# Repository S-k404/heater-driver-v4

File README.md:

<!-- datasheet:banner -->
<p align="center">
  <picture>
    <source media="(prefers-color-scheme: dark)" srcset=".github/assets/banner-dark.svg">
    
  </picture>
</p>
<!-- /datasheet:banner -->

# Heater Driver 12 V / 100 W — v4 (All Through-Hole, Runs Cool, OCP + OTP)

Rev 4.0 · 2026-10-17 · KiCad 9.0 project · 2-layer, **54 × 42 mm** · **100 % through-hole parts**

v4 builds on v3 with three goals:
1. **It can't cook itself.** It uses a 1.3 mΩ MOSFET and adds over-temperature shutdown on top of overcurrent shutdown.
2. **Every part is through-hole.**
3. **A step-by-step placement guide** shows where every part goes.

Start with **`docs/heater_driver_v4_placement_guide.pdf`**.

---

<!-- datasheet:figure -->
## At a glance

<p align="center">
  <picture>
    <source media="(prefers-color-scheme: dark)" srcset=".github/assets/diagram-dark.svg">
    
  </picture>
</p>

| Characteristic | Detail |
| --- | --- |
| **Rating** | 12 V, 100 W (8.33 A) into a heater load; 2-layer board, 54 × 42 mm, 100 % through-hole |
| **Switch** | 1.3 mΩ MOSFET Q1 dissipating about 0.09 W at full load |
| **Protection** | Latching overcurrent (gate off about 7 µs after a short), latching over-temperature at about 84 °C, 15 A fuse, TVS clamp |
| **Verification** | Copper current check to IPC-2221, simulation reports and a step-by-step placement guide in `docs/` |
<!-- /datasheet:figure -->

## 1. Folder contents

| Path | What it is |
|---|---|
| `docs/heater_driver_v4_placement_guide.pdf` | **Assembly guide.** Board map, solder order, full placement table (value, part number, X/Y, orientation, polarity), and one card per component showing exactly where it goes. |
| `docs/heater_driver_v4_test_checklist.pdf` | 24-step bring-up and test (includes an over-temperature test) |
| `docs/heater_driver_v4_schematic.pdf / .png` | Schematic, 6 labelled blocks |
| `docs/heater_driver_v4_layout.pdf`, `*_layout_top/bottom.png` | Layout (top, bottom, assembly pages) |
| `docs/heater_driver_v4_assembly_drawing.pdf` | KiCad assembly drawing (all reference designators) |
| `docs/gerber_check_*.png` | Gerbers re-rendered by an independent viewer (gerbv) |
| `fab/heater_driver_v4_GERBERS_for_fab.zip` | **Upload this to the PCB fab** |
| `bom/heater_driver_v4_BOM.csv`, `bom/heater_driver_v4_CPL_all.csv` | Parts list with part numbers, part positions |
| `heater_driver_v4.kicad_pro / .kicad_sch / .kicad_pcb` | KiCad project (open the `.kicad_pro`) |
| `sim/` | ngspice virtual test (overcurrent, latch, reset, over-temperature) |
| `reports/` | ERC, DRC (with schematic parity), copper current check |
| `scripts/` | Generators (design → schematic → PCB → exports → guide) |

---

## 2. What changed from v3 → v4

| | v3 | **v4** |
|---|---|---|
| Parts | THT + 2 SMD (2512 shunt, 0805) | **100 % through-hole** |
| MOSFET | IRF3205, 8 mΩ → 0.56–0.8 W | **IRFB7430, 1.3 mΩ → ~0.1 W** (≈ +10 °C, no heatsink) |
| Shunt | 2512 SMD on the PCB | **TT/IRC OAR3R010FLF open-air 3 W strap**, stands up in free air, Kelvin sense squares |
| Thermal protection | none | **NTC TH1 next to the shunt and MOSFET.** Above ~84 °C the board latches OFF (same red LED and RESET as overcurrent). |
| Comparator | LM393 | **LM339** (4 comparators: overcurrent trip, latch, over-temperature, spare) |
| Board | 50 × 38 mm | 54 × 42 mm. Grew to fit the new parts; the high-current loop is now a tight ring on the right side. |

Kept from v3:
- isolated, non-inverting PWM input (heater is off when the MCU is unplugged)
- 15 A ATM fuse, 1.5KE18A TVS, 1N5822 flyback
- 11.9 A latching overcurrent trip
- safe RESET (protection stays active while the button is held)

---

## 3. Why it won't burn itself

| Heat source / hazard | v4 figure | Protection |
|---|---|---|
| MOSFET Q1 | 8.33² × 1.3 mΩ = **0.09 W** (≈ 0.15 W hot), simulated 0.08 W | none needed |
| Shunt RS1 | 0.69 W in a **3 W** open-air strap (23 %) | TH1 watches it |
| PCB copper, 8.33 A | ≤ 10.5 °C rise on every path (table below) | both layers, ≥ 5.4 mm |
| Terminals J1/J2 | 8.33 A on 13.5 A rated parts (62 %) | — |
| Short circuit | Gate off ~7 µs after the short, peak ~37 A | latching overcurrent, fuse backup |
| Overheating (blocked airflow, hot enclosure, bad joint) | NTC trips at **~84 °C** (simulated 83.8 °C) | latching over-temperature |
| RESET held into a fault | Pulsed, ~4 A average; fuse intact | protection stays active |
| Supply spikes / reverse kick | 1.5KE18A clamps at 25 V; MOSFET is rated 40 V | TVS1, D1 |
| Wiring fault / last resort | 15 A ATM fuse | F1 |

### Copper current check (`reports/trace_current_check.txt`, IPC-2221, 1 oz)

| Path (8.33 A) | Top + bottom | ΔT |
|---|---|---|
| VIN J1 → F1 | 6.1 + 6.1 mm | 2.8 °C |
| +12V F1 → TVS1 → D1 → J2 | ≥ 3.6 + 4.2 mm | ≤ 6.1 °C |
| HEAT− J2 → Q1 drain | 8.8 + 8.8 mm | 1.5 °C |
| Q1 drain pin neck (TO-220 pitch) | 2.7 + 2.7 mm | 10.5 °C (short neck, conservative) |
| SRC Q1 → RS1 | 2.8 + 2.8 mm | 10.0 °C |
| GND RS1 → J1 | 5.3 + 5.3 mm | 3.5 °C |

---

## 4. Subsystems (numbered on the silkscreen; legend on the bottom side)

1. **ISO IN**: J3, R1, D2, U2 (PC817). Takes 3.3–5 V logic, PWM ≤ 1 kHz.
2. **OCP + OTP LATCH**: U3 (LM339), the shunt filter, the 11.9 A reference, the latch network and RESET injection (R17), and the NTC divider (R18–R20, C9).
3. **GATE DRIVE**: U1 (TC4427A), Q2 fault clamp, R2–R5, ZD1, C2, R14.
4. **POWER IN + PROTECTION**: J1, F1, C1, TVS1, D1, green HEAT LED (D4/R16).
5. **POWER STAGE**: J2, Q1, RS1, TH1.
6. **UI**: SW1 RESET, red FAULT LED (D3/R15).

---

## 5. Verification

- **ERC:** 0 errors, 0 warnings.
- **DRC (with schematic parity):** 0 violations, 0 unconnected pads, 0 footprint errors.
- **Gerbers:** re-rendered with gerbv; outline, copper, drills and silkscreen all match.
- **Routing:** 3 signal vias (plus 3 ground stitching vias), every segment at 0/45/90°. High-current copper is hand-placed; signal traces were autorouted with the optimizer on.
- **Simulation** (`sim/sim_overview.png`):

| Scenario | Result |
|---|---|
| Normal running | 8.1 A, Vgs 11.7 V, Q1 0.08 W |
| Power-up | No false trip (FAULT 0.11 V) |
| Dead short | Off in ~7 µs, latched |
| RESET | Normal operation resumes |
| RESET held into a short | Pulsed, 4.0 A average |
| NTC ramped 25 → 105 °C | Trips at **83.8 °C**, latched off |

---

## 6. Ordering and building

**PCB:** upload `fab/heater_driver_v4_GERBERS_for_fab.zip` and choose:
- 2 layers, FR-4, 1.6 mm, 1 oz (2 oz optional), 54 × 42 mm
- HASL or ENIG finish
- minimums used: 0.3 mm track, 0.2 mm clearance, 0.35 mm smallest drill

**Parts:** `bom/heater_driver_v4_BOM.csv` lists all 46 parts (every one through-hole) with manufacturer part numbers.

**Building:** follow the placement guide in solder order:
1. resistors
2. small diodes
3. ceramic capacitors
4. ICs
5. Q2, LEDs, NTC
6. switch
7. big diodes
8. C1
9. Q1 and RS1
10. fuse holder and terminals

Then work through the test checklist.

---

## 7. Honest notes

- The board is **54 × 42 mm**: 9 % larger than v2 and 19 % larger than v3. That's the cost of going 100 % through-hole and adding over-temperature protection.
- **IRFB7430PBF** is the primary MOSFET. IRLB3034PBF (1.7 mΩ) is a drop-in alternative; one distributor lists it as no longer manufactured, so check stock.
- **OAR3R010FLF:** lead pitch (15.24 mm) and lead diameter (1.02 mm) come from distributor listings. Check them against the TT Electronics OAR datasheet before ordering the board.
- **Silkscreen designators:** C5, C7, R7, R13, J1 and J2 don't fit visibly on the dense top silkscreen. The placement guide and assembly drawing show every part.
- **The ~84 °C threshold** is set by R20 (11 k) and depends on how well TH1 touches the shunt/MOSFET copper. Bend it so the bead leans against the RS1 strap.
- **Simulation scope:** the simulation uses behavioural models for the PC817, TC4427 and LM339. Treat it as a logic and timing check, then run the real tests in the checklist.

## License

MIT. See [LICENSE](LICENSE).

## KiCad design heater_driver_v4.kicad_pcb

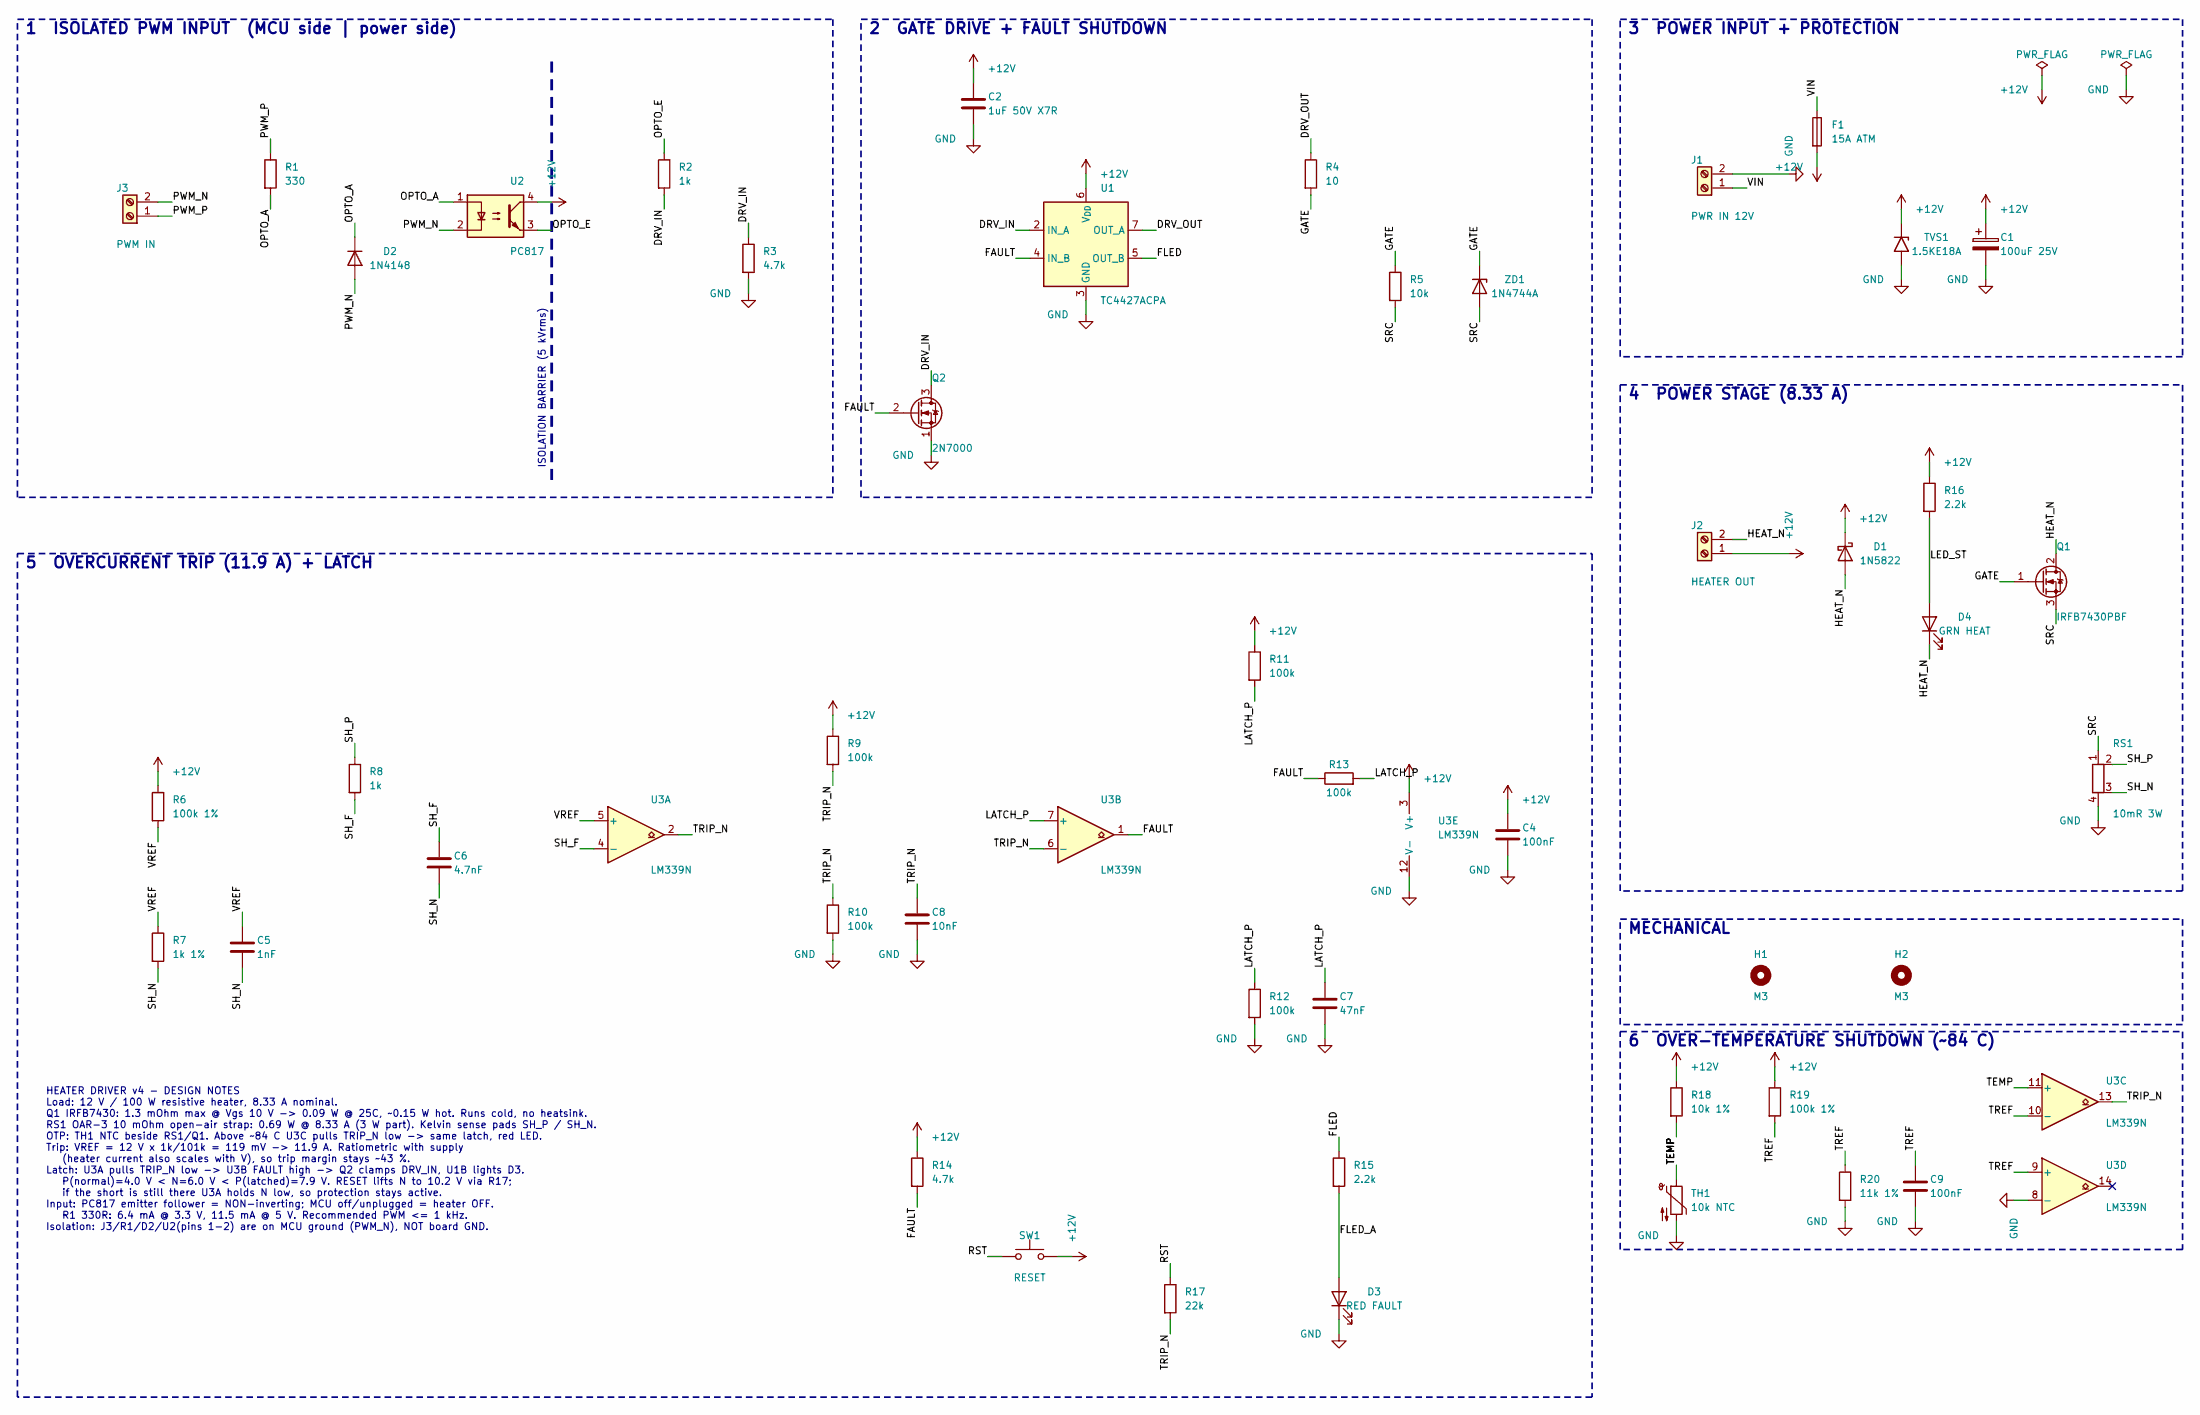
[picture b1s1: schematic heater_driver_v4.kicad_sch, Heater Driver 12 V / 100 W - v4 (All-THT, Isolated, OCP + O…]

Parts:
C1: 100uF 25V; CP_Radial_D6.3mm_P2.50mm; MPN Panasonic EEU-FR1E101 (low ESR, 6.3x11.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
C2: 1uF 50V X7R; C_Rect_L4.0mm_W2.5mm_P2.50mm; MPN TDK FG28X7R1H105KRT06
C4, C9: 100nF; C_Disc_D3.0mm_W1.6mm_P2.50mm; MPN KEMET C320C104K5R5TA
C5: 1nF; C_Disc_D3.0mm_W1.6mm_P2.50mm; MPN KEMET C315C102K5R5TA
C6: 4.7nF; C_Disc_D3.0mm_W1.6mm_P2.50mm; MPN KEMET C315C472K5R5TA
C7: 47nF; C_Disc_D3.0mm_W1.6mm_P2.50mm; MPN KEMET C320C473K5R5TA
C8: 10nF; C_Disc_D3.0mm_W1.6mm_P2.50mm; MPN KEMET C315C103K5R5TA
D1: 1N5822; D_DO-201AD_P5.08mm_Vertical_AnodeUp; MPN onsemi 1N5822
D2: 1N4148; D_DO-35_SOD27_P2.54mm_Vertical_AnodeUp; MPN onsemi 1N4148
D3: RED FAULT; LED_D3.0mm; MPN Kingbright WP7104ID
D4: GRN HEAT; LED_D3.0mm; MPN Kingbright WP7104GD
F1: 15A ATM; Fuseholder_Blade_Mini_Keystone_3568; MPN Keystone 3568 + Littelfuse 0297015 (15A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
H1, H2: M3; MountingHole_3.2mm_M3
J1: PWR IN 12V; TerminalBlock_Phoenix_MKDS-1,5-2-5.08_1x02_P5.08mm_Horizont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; MPN Phoenix 1729128 (MKDS 1,5/2-5,08, 13.5A)
J2: HEATER OUT; TerminalBlock_Phoenix_MKDS-1,5-2-5.08_1x02_P5.08mm_Horizont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; MPN Phoenix 1729128 (MKDS 1,5/2-5,08, 13.5A)
J3: PWM IN; TerminalBlock_Phoenix_MPT-0,5-2-2.54_1x02_P2.54mm_Horizontal; MPN Phoenix 1725656 (MPT 0,5/2-2,54)
Q1: IRFB7430PBF; TO-220-3_Vertical; MPN Infineon IRFB7430PBF (alt: IRLB3034PBF)
Q2: 2N7000; TO-92_Inline; MPN onsemi 2N7000
R1: 330; R_Axial_DIN0207_L6.3mm_D2.5mm_P2.54mm_Vertical; MPN Yageo MFR-25FBF52-330R
R2, R8: 1k; R_Axial_DIN0207_L6.3mm_D2.5mm_P2.54mm_Vertical; MPN Yageo MFR-25FBF52-1K
R3, R14: 4.7k; R_Axial_DIN0207_L6.3mm_D2.5mm_P2.54mm_Vertical; MPN Yageo MFR-25FBF52-4K7
R4: 10; R_Axial_DIN0207_L6.3mm_D2.5mm_P2.54mm_Vertical; MPN Yageo MFR-25FBF52-10R
R5: 10k; R_Axial_DIN0207_L6.3mm_D2.5mm_P2.54mm_Vertical; MPN Yageo MFR-25FBF52-10K
R6, R19: 100k 1%; R_Axial_DIN0207_L6.3mm_D2.5mm_P2.54mm_Vertical; MPN Yageo MFR-25FBF52-100K
R7: 1k 1%; R_Axial_DIN0207_L6.3mm_D2.5mm_P2.54mm_Vertical; MPN Yageo MFR-25FBF52-1K
R9, R10, R11, R12, R13: 100k; R_Axial_DIN0207_L6.3mm_D2.5mm_P2.54mm_Vertical; MPN Yageo MFR-25FBF52-100K
R15, R16: 2.2k; R_Axial_DIN0207_L6.3mm_D2.5mm_P2.54mm_Vertical; MPN Yageo MFR-25FBF52-2K2
R17: 22k; R_Axial_DIN0207_L6.3mm_D2.5mm_P2.54mm_Vertical; MPN Yageo MFR-25FBF52-22K
R18: 10k 1%; R_Axial_DIN0207_L6.3mm_D2.5mm_P2.54mm_Vertical; MPN Yageo MFR-25FBF52-10K
R20: 11k 1%; R_Axial_DIN0207_L6.3mm_D2.5mm_P2.54mm_Vertical; MPN Yageo MFR-25FBF52-11K
RS1: 10mR 3W; R_Shunt_OAR3_P15.24mm_Kelvin; MPN TT Electronics/IRC OAR3R010FLF
SW1: RESET; SW_PUSH_6mm; MPN Omron B3F-1000
TH1: 10k NTC; C_Disc_D3.0mm_W2.0mm_P2.50mm; MPN Vishay NTCLE100E3103JB0
TVS1: 1.5KE18A; D_DO-201AD_P5.08mm_Vertical_AnodeUp; MPN Littelfuse 1.5KE18A
U1: TC4427ACPA; DIP-8_W7.62mm; MPN Microchip TC4427ACPA (DIP-8)
U2: PC817; DIP-4_W7.62mm; MPN Sharp PC817X / Everlight EL817
U3: LM339N; DIP-14_W7.62mm; MPN TI LM339N (DIP-14)
ZD1: 1N4744A; D_DO-41_SOD81_P2.54mm_Vertical_AnodeUp; MPN onsemi 1N4744A

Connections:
+12V: C1.1, C2.1, C4.1, D1.1 (K), F1.2, J2.1, R6.1, R9.1, R11.1, R14.1, R16.1, R18.1, R19.1, SW1.2, TVS1.1 (A1), U1.6 (V_{DD}), U2.4, U3.3 (V+)
/DRV_IN: Q2.3 (D), R2.2, R3.1, U1.2 (IN_A)
/DRV_OUT: R4.1, U1.7 (OUT_A)
/FAULT: Q2.2 (G), R13.1, R14.2, U1.4 (IN_B), U3.1
/FLED: R15.1, U1.5 (OUT_B)
/FLED_A: D3.2 (A), R15.2
/GATE: Q1.1 (G), R4.2, R5.1, ZD1.1 (K)
/HEAT_N: D1.2 (A), D4.1 (K), J2.2, Q1.2 (D)
/LATCH_P: C7.1, R11.2, R12.1, R13.2, U3.7 (+)
/LED_ST: D4.2 (A), R16.2
/OPTO_A: D2.1 (K), R1.2, U2.1
/OPTO_E: R2.1, U2.3
/PWM_N: D2.2 (A), J3.2, U2.2
/PWM_P: J3.1, R1.1
/RST: R17.1, SW1.1
/SH_F: C6.1, R8.2, U3.4 (-)
/SH_N: C5.2, C6.2, R7.2, RS1.3
/SH_P: R8.1, RS1.2
/SRC: Q1.3 (S), R5.2, RS1.1, ZD1.2 (A)
/TEMP: R18.2, TH1.1, U3.11 (+)
/TREF: C9.1, R19.2, R20.1, U3.9 (+), U3.10 (-)
/TRIP_N: C8.1, R9.2, R10.1, R17.2, U3.2, U3.6 (-), U3.13
/VIN: F1.1, J1.1
/VREF: C5.1, R6.2, R7.1, U3.5 (+)
GND: C1.2, C2.2, C4.2, C7.2, C8.2, C9.2, D3.1 (K), J1.2, Q2.1 (S), R3.2, R10.2, R12.2, R20.2, RS1.4, TH1.2, TVS1.2 (A2), U1.3 (GND), U3.8 (-), U3.12 (V-)

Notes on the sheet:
1 ISOLATED PWM INPUT (MCU side | power side)
2 GATE DRIVE + FAULT SHUTDOWN
3 POWER INPUT + PROTECTION
4 POWER STAGE (8.33 A)
5 OVERCURRENT TRIP (11.9 A) + LATCH
MECHANICAL
6 OVER-TEMPERATURE SHUTDOWN (~84 C)
ISOLATION BARRIER (5 kVrms)
HEATER DRIVER v4 - DESIGN NOTES Load: 12 V / 100 W resistive heater, 8.33 A nominal. Q1 IRFB7430: 1.3 mOhm max @ Vgs 10 V -> 0.09 W @ 25C, ~0.15 W hot. Runs cold, no heatsink. RS1 OAR-3 10 mOhm open-air strap: 0.69 W @ 8.33 A (3 W part). Kelvin sense pads SH_P / SH_N. OTP: TH1 NTC beside RS1/Q1. Ab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

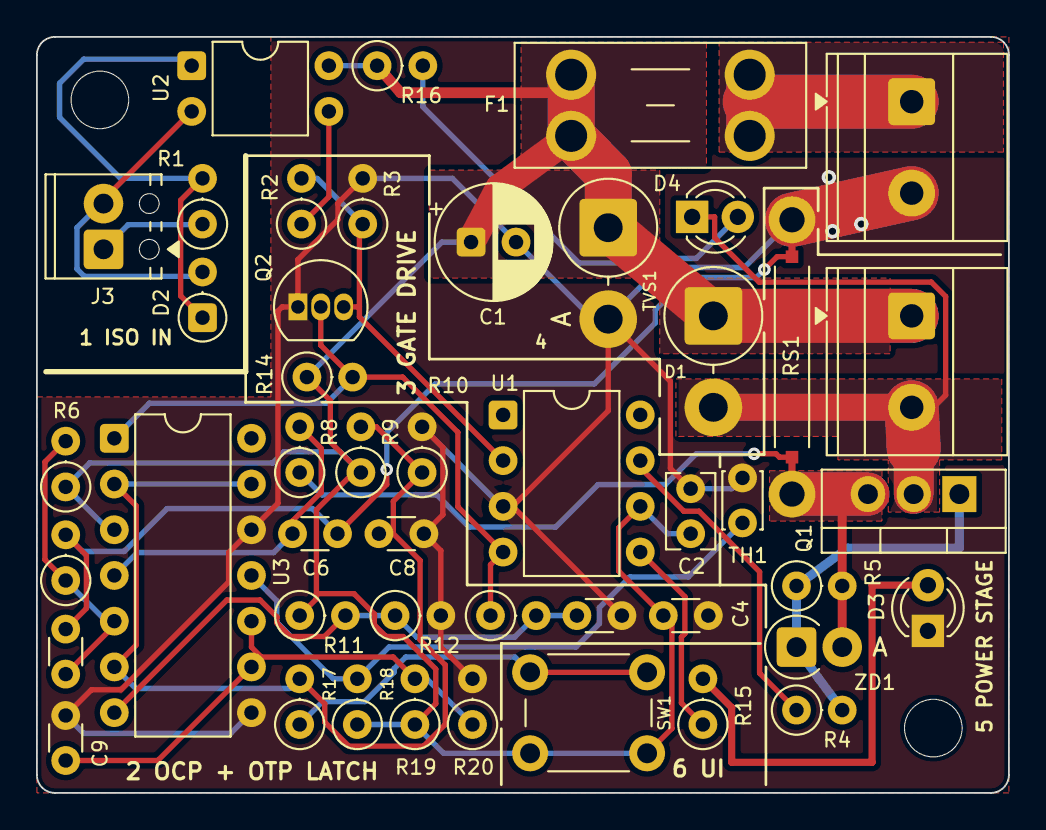
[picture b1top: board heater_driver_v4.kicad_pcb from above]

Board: 2 copper layers, 54.0 x 42.0 mm, 48 parts (0 on the bottom side), 25 nets.

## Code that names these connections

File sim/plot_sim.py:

"""Plot ngspice virtual-test results (run: ngspice -b heater_driver_v3_virtual_test.cir; python3 plot_sim.py)"""
import numpy as np, matplotlib
matplotlib.use('Agg')
import matplotlib.pyplot as plt
d = np.loadtxt('heater_driver_v4_sim.dat')
t = d[:, 0] * 1e3
names = ['pwm', 'iheat', 'vgs', 'fault', 'trip_n', 'latch_p', 'sh_f', 'vref', 'heat_n', 'p12', 'tdeg', 'temp', 'tref']
c = {n: d[:, 2 * i + 1] for i, n in enumerate(names)}
fig, ax = plt.subplots(6, 1, figsize=(11, 13), sharex=True)
ax[0].plot(t, c['pwm'], color='#555'); ax[0].set_ylabel('PWM in (V)'); ax[0].set_ylim(-0.3, 4.8)
ax[1].plot(t, c['iheat'], color='#c0392b'); ax[1].axhline(11.9, ls='--', color='k', lw=0.8)
ax[1].text(0.2, 13, 'trip 11.9 A', fontsize=8); ax[1].set_ylabel('I heater (A)')
ax[2].plot(t, c['vgs'], color='#2c7fb8'); ax[2].set_ylabel('Q1 Vgs (V)')
ax[3].plot(t, c['fault'], color='#d35400', label='FAULT'); ax[3].plot(t, c['trip_n'], color='#27ae60', label='TRIP_N (N)')
ax[3].plot(t, c['latch_p'], color='#8e44ad', label='LATCH_P (P)'); ax[3].legend(fontsize=8, loc='upper left'); ax[3].set_ylabel('latch (V)')
ax[4].plot(t, c['p12'], color='#333'); ax[4].set_ylabel('+12V rail (V)')
ax[5].plot(t, c['tdeg'], color='#c0392b', label='NTC temperature (C)'); ax[5].axhline(84, ls='--', color='k', lw=0.8)
ax[5].text(0.2, 86, 'OTP trip ~84 C', fontsize=8); ax[5].set_ylabel('NTC temp (C)'); ax[5].set_xlabel('time (ms)')
for a in ax:
    a.grid(alpha=0.3)
    for x in (2, 8.3, 10, 12, 13, 14, 14.2, 15.8, 16, 17): a.axvline(x, color='grey', lw=0.6, ls=':')
for x, l in [(0.1, 'power-up'), (2.05, 'PWM 1 kHz 50%'), (8.35, 'SHORT'), (10.05, 'short off'), (12.05, 'RESET'), (13.6, 'RESET held'), (14.25, '+SHORT'), (16.1, 'released'), (17.1, 'OVER-TEMP ramp')]:
    ax[0].text(x, 3.7, l, fontsize=8)
fig.suptitle('Heater driver v4 - virtual test (ngspice): power-up, PWM, short trip, latch, reset, RESET held into short, over-temperature', fontsize=11)
fig.tight_layout(); fig.savefig('sim_overview.png', dpi=110)
m = (t > 8.29) & (t < 8.33)
us = t[m] * 1000 - 8300
fig, ax = plt.subplots(3, 1, figsize=(9, 7), sharex=True)
ax[0].plot(us, c['iheat'][m], color='#c0392b'); ax[0].axhline(11.9, ls='--', color='k', lw=0.8); ax[0].set_ylabel('I (A)')
ax[1].plot(us, c['sh_f'][m] * 1000, label='SH_F (filtered shunt)'); ax[1].plot(us, c['vref'][m] * 1000, label='VREF'); ax[1].set_ylabel('mV'); ax[1].legend(fontsize=8)
ax[2].plot(us, c['vgs'][m], label='Q1 Vgs'); ax[2].plot(us, c['fault'][m], label='FAULT'); ax[2].set_ylabel('V'); ax[2].legend(fontsize=8)
ax[2].set_xlabel('time after short applied (us)')
for a in ax: a.grid(alpha=0.3)
fig.suptitle('Short-circuit zoom: gate off ~8 us after short, peak 37 A, fault latched', fontsize=11)
fig.tight_layout(); fig.savefig('sim_short_zoom.png', dpi=110)
print('ok')
